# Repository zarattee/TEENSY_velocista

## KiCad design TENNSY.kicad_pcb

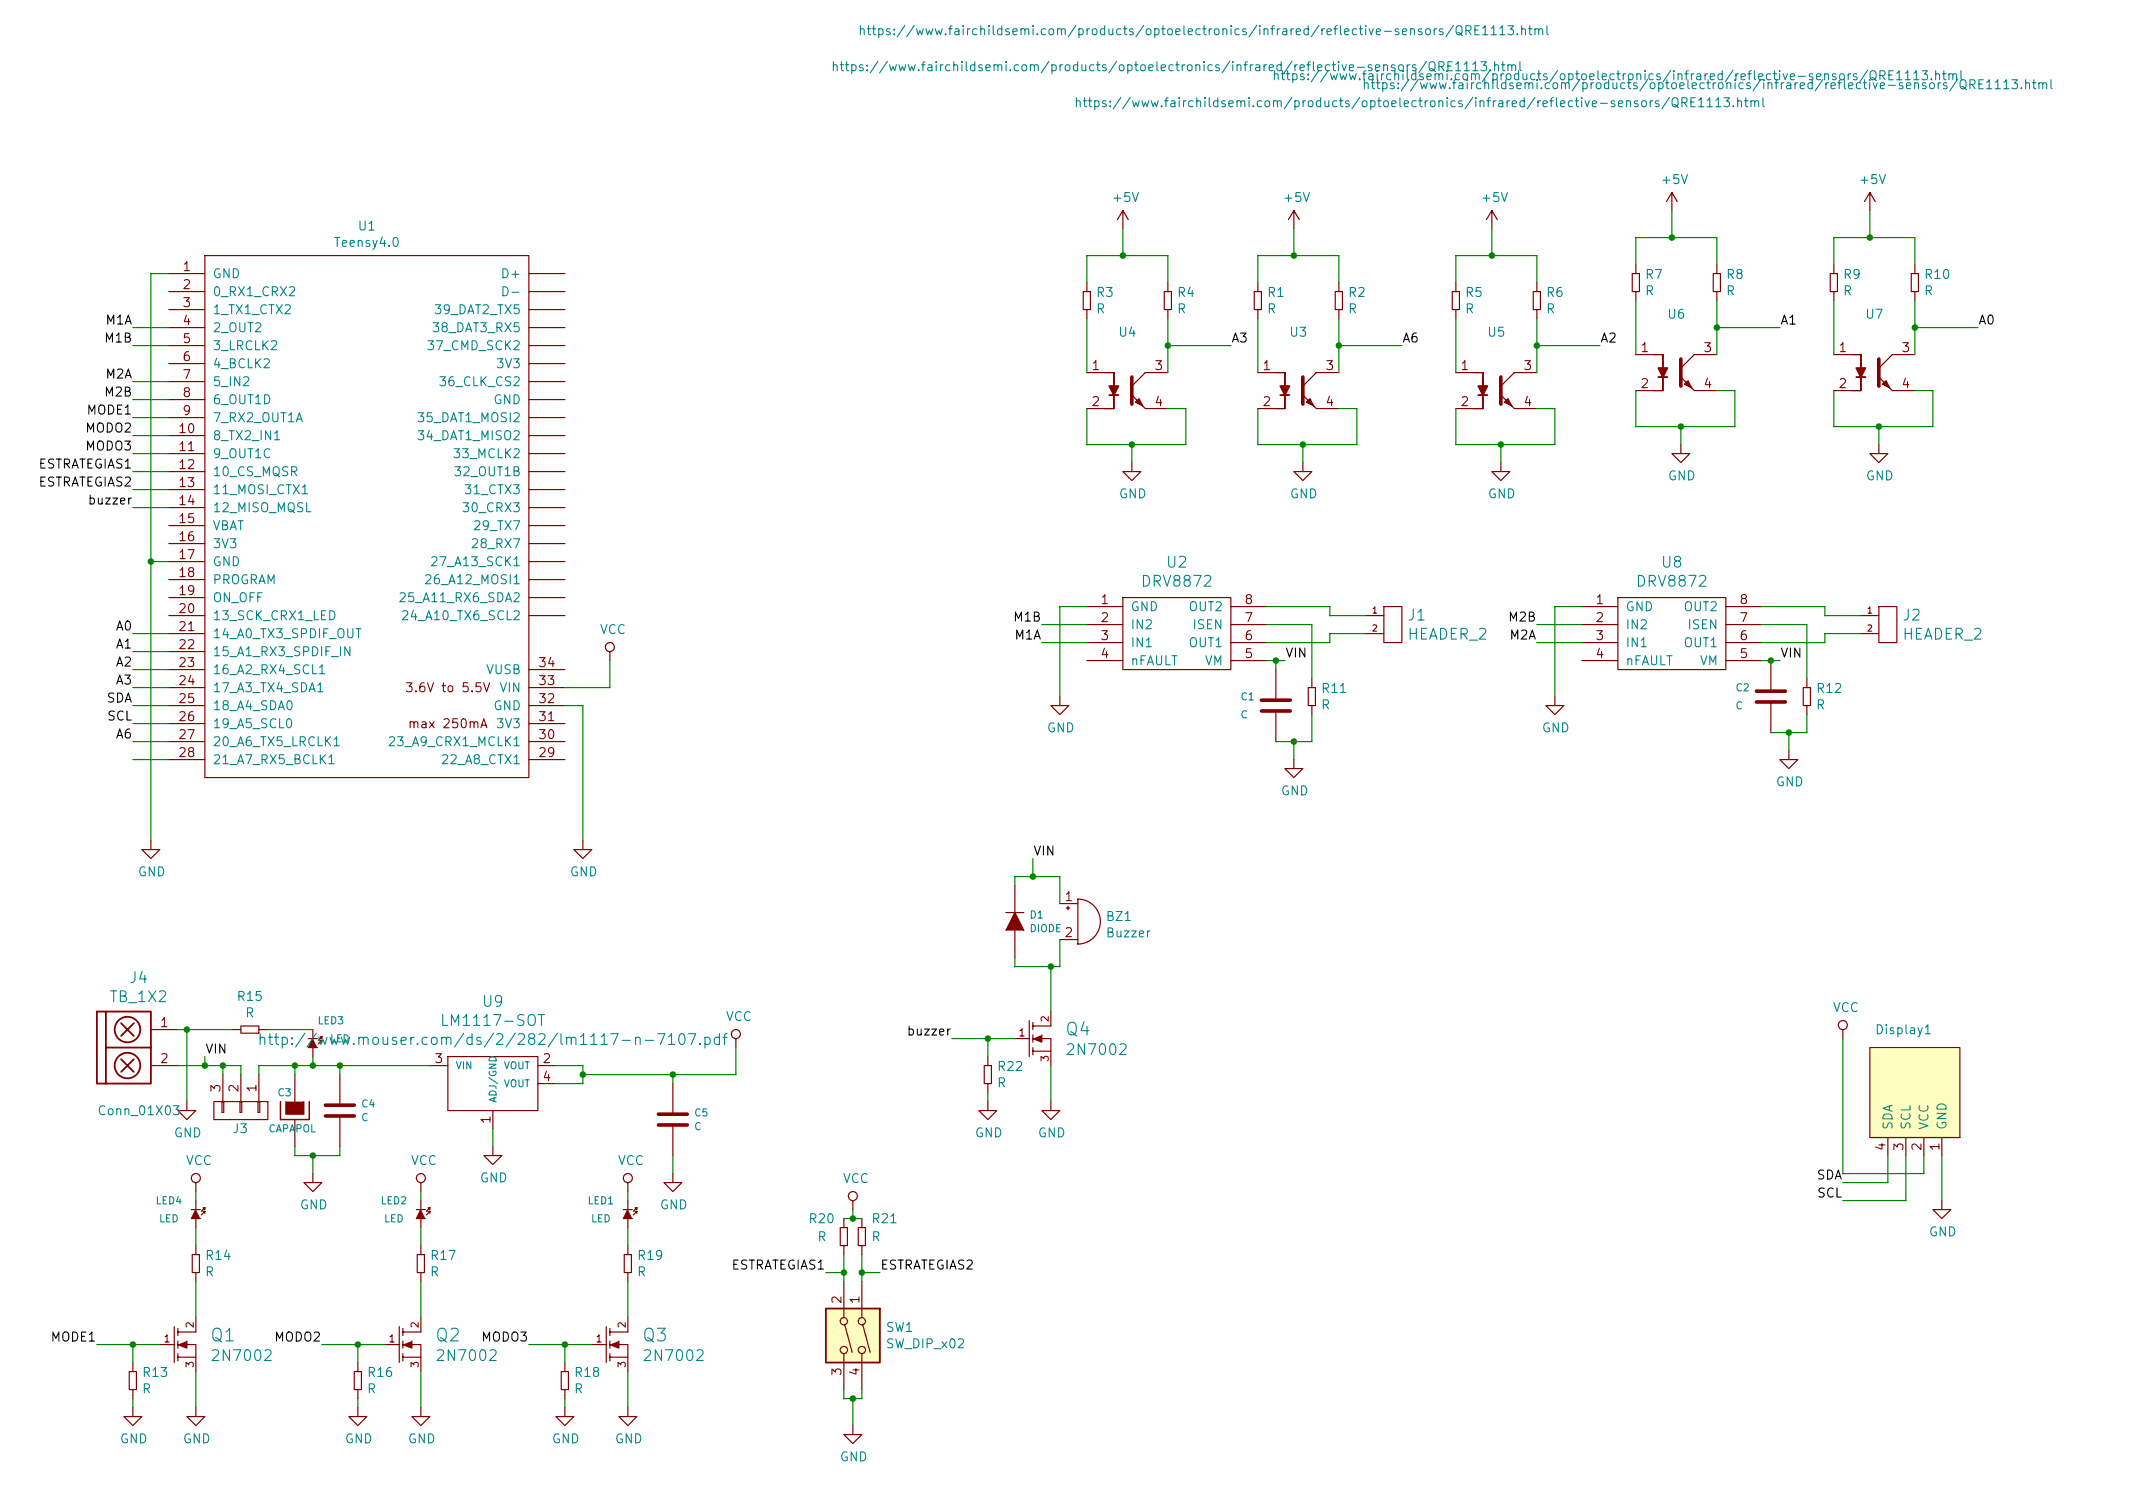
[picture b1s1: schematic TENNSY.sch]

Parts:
BZ1: Buzzer; Buzzer_12mm
C1, C2: C; CAP_ELEC_SMD_4X5.5
C3: CAPAPOL; CAP_ELEC_SMD_4X5.5
C4, C5: C; C_1206
D1: DIODE; sod123
Display1: SSD1306-SSD1306-128x64_OLED; 128x64OLED
J1, J2: HEADER_2; Pin_strip_2
J3: Conn_01X03; Pin_Strip_3
J4: TB_1X2; BORNERA2_DUO
LED1, LED2, LED3, LED4: LED; LED_1206
Q1, Q2, Q3, Q4: 2N7002; SOT23
R1, R2, R3, R4, R5, R6, R7, R8, R9, R10, R11, R12, R13, R14, R15, R16, R17, R18, R19, R20, R21, R22: R; R_1206
SW1: SW_DIP_x02; Dip_SW_2-300
U1: Teensy4.0; Teensy40
U2, U8: DRV8872; SSOP-8
U3, U4, U5, U6, U7: QRE1113; QRE1113GR
U9: LM1117-SOT; SOT223

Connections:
+5V: R1.1, R2.1, R3.1, R4.1, R5.1, R6.1, R7.1, R8.1, R9.1, R10.1
/A0: R10.2, U1.21 (14_A0_TX3_SPDIF_OUT), U7.3
/A1: R8.2, U1.22 (15_A1_RX3_SPDIF_IN), U6.3
/A2: R6.2, U1.23 (16_A2_RX4_SCL1), U5.3
/A3: R4.2, U1.24 (17_A3_TX4_SDA1), U4.3
/A6: R2.2, U1.27 (20_A6_TX5_LRCLK1), U3.3
/ESTRATEGIAS1: R20.2, SW1.2, U1.12 (10_CS_MQSR)
/ESTRATEGIAS2: R21.2, SW1.1, U1.13 (11_MOSI_CTX1)
/M1A: U1.4 (2_OUT2), U2.3 (IN1)
/M1B: U1.5 (3_LRCLK2), U2.2 (IN2)
/M2A: U1.7 (5_IN2), U8.3 (IN1)
/M2B: U1.8 (6_OUT1D), U8.2 (IN2)
/MODE1: Q1.1 (G), R13.1, U1.9 (7_RX2_OUT1A)
/MODO2: Q2.1 (G), R16.1, U1.10 (8_TX2_IN1)
/MODO3: Q3.1 (G), R18.1, U1.11 (9_OUT1C)
/SCL: Display1.3 (SCL), U1.26 (19_A5_SCL0)
/SDA: Display1.4 (SDA), U1.25 (18_A4_SDA0)
/VIN: BZ1.1 (-), C1.1, C2.1, D1.2 (K), J3.2, J3.3, J4.2, U2.5 (VM), U8.5 (VM)
/buzzer: Q4.1 (G), R22.1, U1.14 (12_MISO_MQSL)
GND: C1.2, C2.2, C3.2, C4.2, C5.2, Display1.1 (GND), J4.1, Q1.3 (S), Q2.3 (S), Q3.3 (S), Q4.3 (S), R11.2, R12.2, R13.2, R15.2, R16.2, R18.2, R22.2, SW1.3, SW1.4, U1.1 (GND), U1.17 (GND), U1.32 (GND), U2.1 (GND), U3.2, U3.4, U4.2, U4.4, U5.2, U5.4, U6.2, U6.4, U7.2, U7.4, U8.1 (GND), U9.1 (ADJ/GND)
unnamed: BZ1.2 (+), D1.1 (A), Q4.2 (D)
unnamed: C3.1, C4.1, J3.1, LED3.1 (A), U9.3 (VIN)
unnamed: J1.1, U2.8 (OUT2)
unnamed: J1.2, U2.6 (OUT1)
unnamed: J2.1, U8.8 (OUT2)
unnamed: J2.2, U8.6 (OUT1)
unnamed: LED1.1 (A), R19.1
unnamed: LED2.1 (A), R17.1
unnamed: LED3.2 (K), R15.1
unnamed: LED4.1 (A), R14.1
unnamed: Q1.2 (D), R14.2
unnamed: Q2.2 (D), R17.2
unnamed: Q3.2 (D), R19.2
unnamed: R1.2, U3.1
unnamed: R3.2, U4.1
unnamed: R5.2, U5.1
unnamed: R7.2, U6.1
unnamed: R9.2, U7.1
unnamed: R11.1, U2.7 (ISEN)
unnamed: R12.1, U8.7 (ISEN)
VCC: C5.1, Display1.2 (VCC), LED1.2 (K), LED2.2 (K), LED4.2 (K), R20.1, R21.1, U1.33 (VIN), U9.2 (VOUT), U9.4 (VOUT)

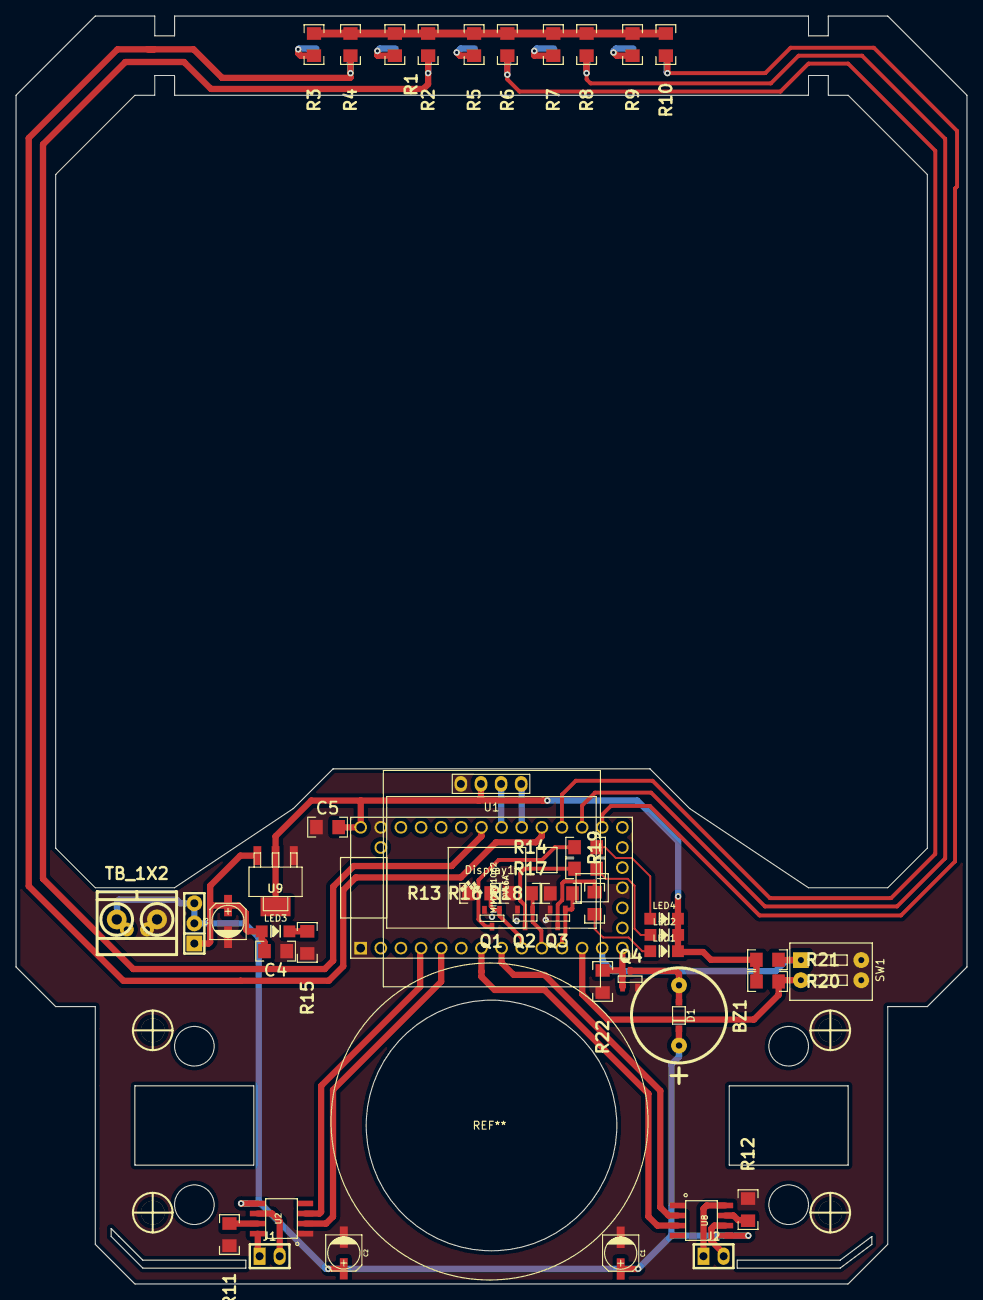
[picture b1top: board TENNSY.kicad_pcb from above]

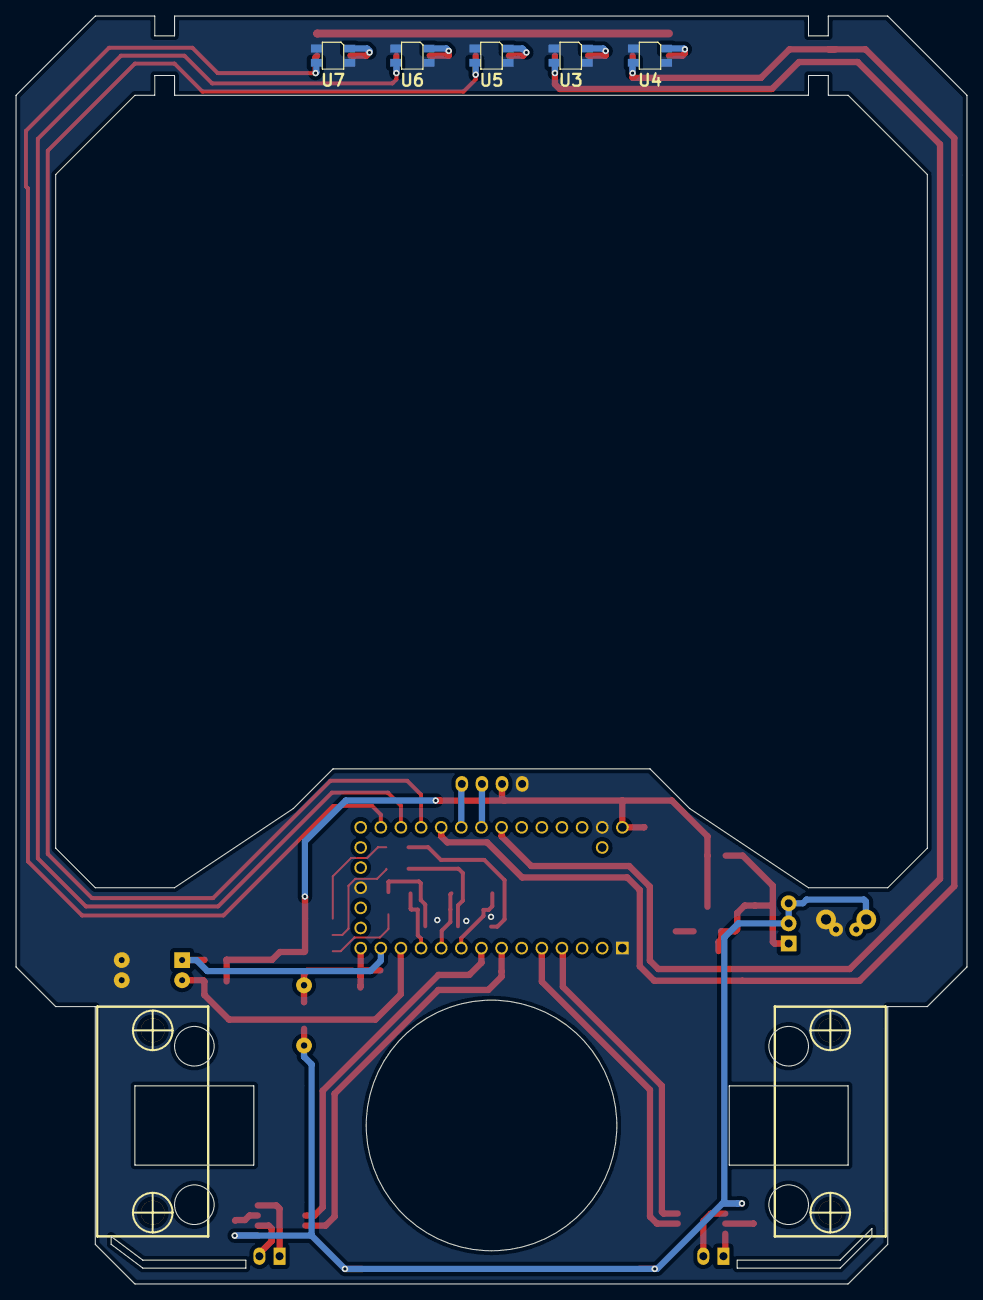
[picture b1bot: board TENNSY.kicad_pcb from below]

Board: 2 copper layers, 120.0 x 160.0 mm, 54 parts (7 on the bottom side), 41 nets.

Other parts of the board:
Pololu_Micro_Gear_Motor: VAL**; Pololu_Micro_Con_Soporte_Simple
Pololu_Micro_Gear_Motor#2: VAL**; Pololu_Micro_Con_Soporte_Simple

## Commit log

2020-12-13 archicos pcb
    pcb
2020-12-13 modificaciones
    se movio archivos a la carpeta principal
2020-12-23 modificaciones
    se arego imagenes 3d y modificacion en el sch y pcb
2021-07-08 modificaciones
    se modifico el pcb
2021-07-08 modificaciones
    se modifico sch,pcb y se agrego modelos 3d
2021-07-08 modificacion
    se agrego carpeta de vista 3d de la turbina
2021-07-08 modificaciones
    se modifico sch,pcb:
    se agrego una llave
2021-07-10 MODIFICACIONES
    se modifico el sch y pcb
2021-07-17 modificaciones
    se realizo modificaciones en el sch y pcb, proyecto en su 70% para su finalizacion
2021-07-18 modificaciones
    se termino pcb,se agregaron: buzzer,imagen de sch de un modulo gitoscopio
